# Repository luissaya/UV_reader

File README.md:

# UV reader

Read UV-A and UV-B radiation each minute and save the values with timestamp on an micro SD card.

## Pins

| Pin # | Name      | Pin name | Description                   |
| ----- | --------- | -------- | ----------------------------- |
| 1     | RST       | -        | Reset the chip                |
| 2     | ADC       | A0       | Read the UV sensor            |
| 3     | RESET     | -        | Enable, must be HIGH          |
| 4     | Deepsleep | 16       | Deepsleep, connect to RST pin |
| 5     | CSK       | 14       | SPI pin                       |
| 6     | MISO      | 12       | SPI pin                       |
| 7     | MOSI      | 13       | SPI pin                       |
| 16    | CS        | 15       | SPI pin                       |
| 17    | LED       | 2        | LED, turn on in LOW           |
| 18    | BOOT      | 0        | To flash the firmware         |
| 19    | SDA       | 4        | I2C pin                       |
| 20    | SCL       | 5        | I2C pin                       |
| 21    | RX        | -        | UART pin                      |
| 22    | TX        | -        | UART pin                      |
  
| Label | GPIO   | Input         | Output                | Notes                                                           |
| ----- | ------ | ------------- | --------------------- | --------------------------------------------------------------- |
| D0    | GPIO16 | no interrupt  | no PWM or I2C support | HIGH at boot used to wake up from deep sleep                    |
| D1    | GPIO5  | OK            | OK                    | often used as SCL (I2C)                                         |
| D2    | GPIO4  | OK            | OK                    | often used as SDA (I2C)                                         |
| D3    | GPIO0  | pulled up     | OK                    | connected to FLASH button, boot fails if pulled LOW             |
| D4    | GPIO2  | pulled up     | OK                    | HIGH at bootconnected to on-board LED, boot fails if pulled LOW |
| D5    | GPIO14 | OK            | OK                    | SPI (SCLK)                                                      |
| D6    | GPIO12 | OK            | OK                    | SPI (MISO)                                                      |
| D7    | GPIO13 | OK            | OK                    | SPI (MOSI)                                                      |
| D8    | GPIO15 | pulled to GND | OK                    | SPI (CS), Boot fails if pulled HIGH                             |
| RX    | GPIO3  | OK            | RX pin                | HIGH at boot                                                    |
| TX    | GPIO1  | TX pin        | OK                    | HIGH at boot, debug output at boot, boot fails if pulled LOW    |
| A0    | ADC0   | Analog        | Input                 | X                                                               |

## Calibration

Calculus to obtain the reference voltaje for genering UV intensity:

- `Vref` is the reference value to obtain:
- `Vout`: is read with multimeter.
- `Nread`: is read with ADC.

```bash
Vref = Vout x 1023 / Nread
Vref = 3.684
```

In the main code, put the next expression:  

```bash
Vout = Vref x Nread / 1023
Vout = 3.684 x Nread / 1023
```

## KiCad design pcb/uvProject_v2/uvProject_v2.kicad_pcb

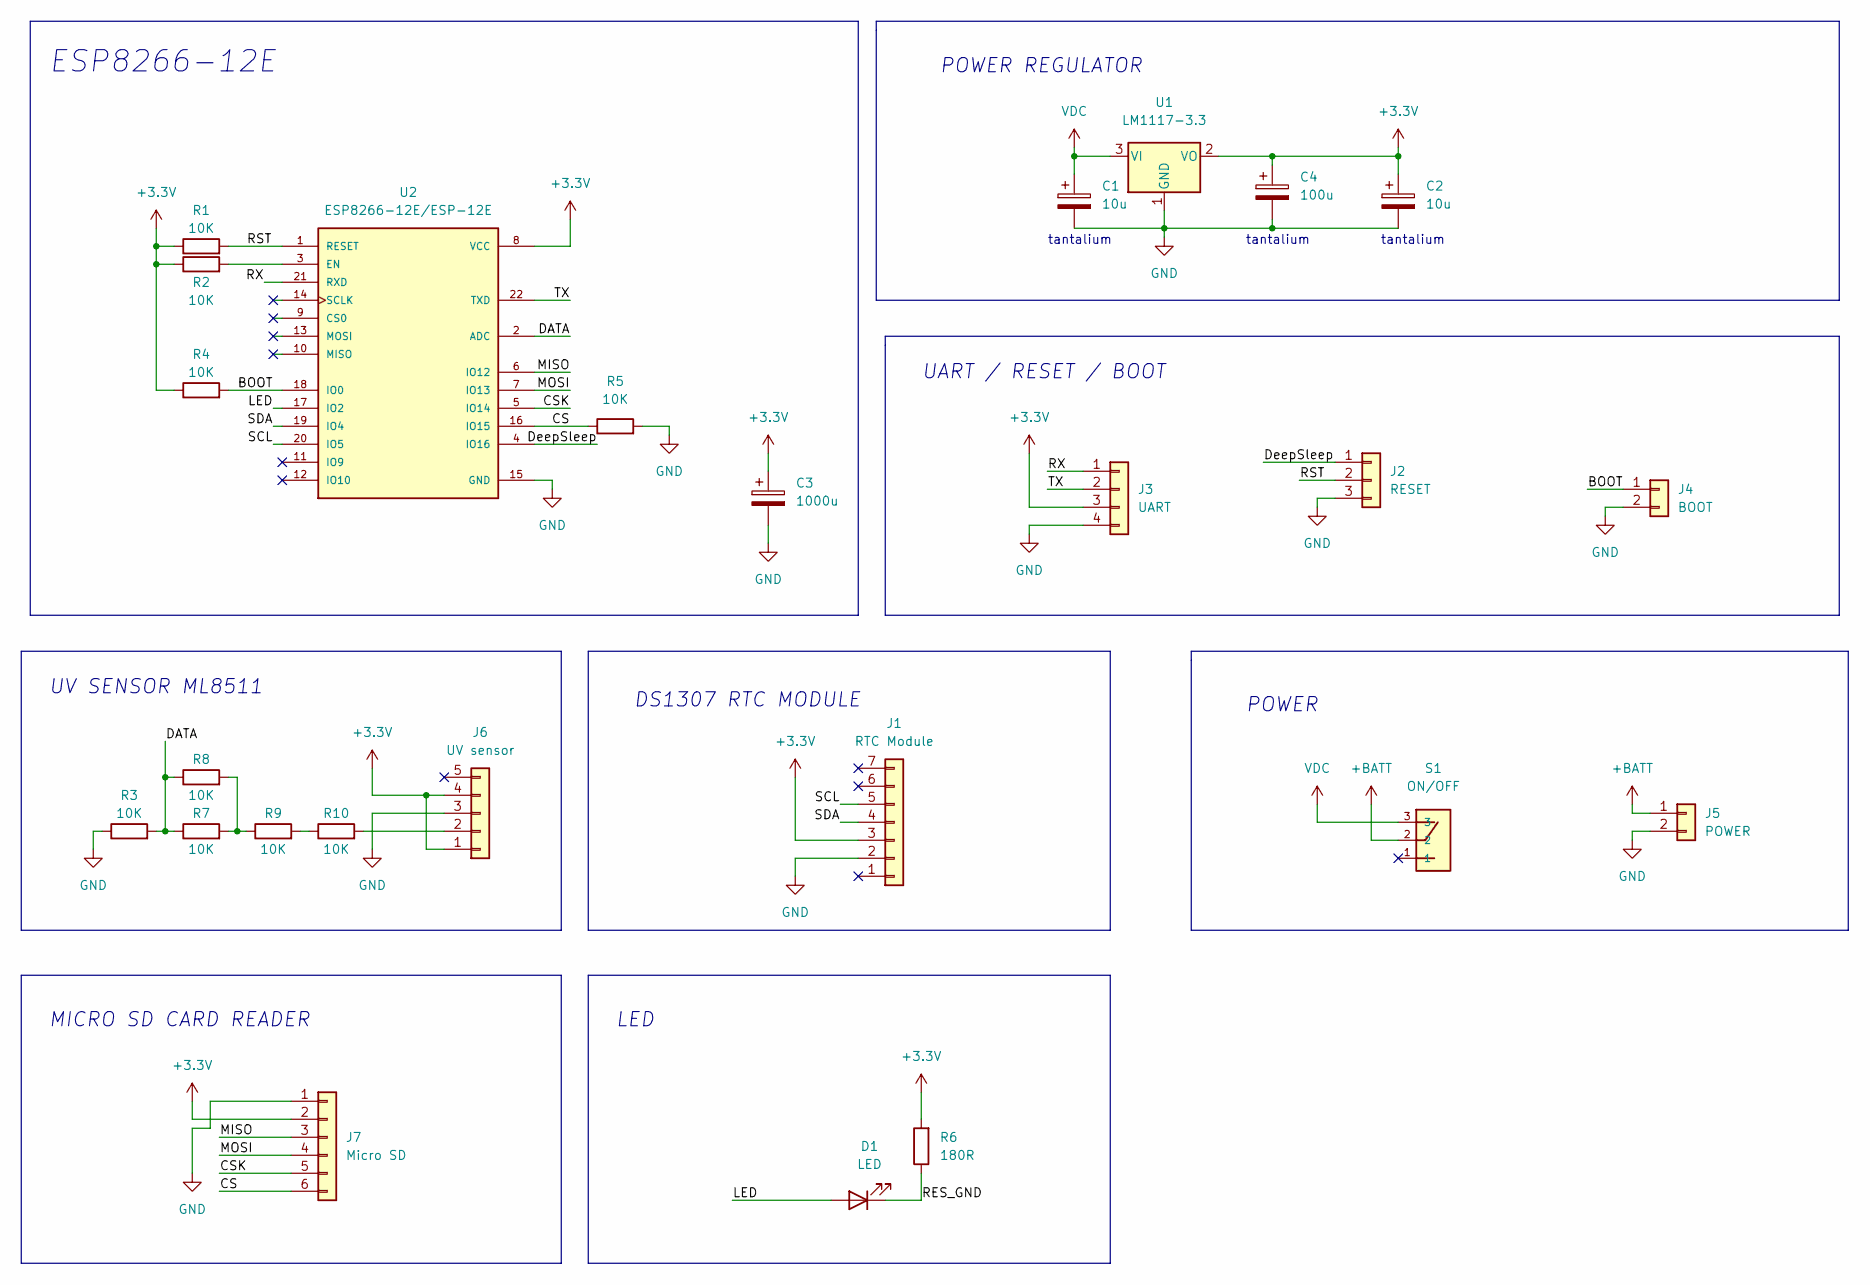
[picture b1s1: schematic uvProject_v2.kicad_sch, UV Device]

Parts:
C1, C2: 10u; C_0603_1608Metric_Pad1.08x0.95mm_HandSolder
C3: 1000u; CP_Radial_D8.0mm_P3.50mm
C4: 100u; C_0805_2012Metric_Pad1.18x1.45mm_HandSolder
D1: LED; LED_D3.0mm
J1: RTC Module; PinHeader_1x07_P2.54mm_Vertical
J2: RESET; PinHeader_1x03_P2.54mm_Vertical
J3: UART; PinSocket_1x04_P2.54mm_Vertical
J4: BOOT; PinHeader_1x02_P2.54mm_Vertical
J5: POWER; PinHeader_1x02_P2.54mm_Vertical
J6: UV sensor; PinSocket_1x05_P2.54mm_Vertical
J7: Micro SD; PinHeader_1x06_P2.54mm_Vertical
R1, R2, R3, R4, R5, R7, R8, R9, R10: 10K; R_1206_3216Metric_Pad1.30x1.75mm_HandSolder
R6: 180R; R_1206_3216Metric_Pad1.30x1.75mm_HandSolder
S1: ON/OFF; SW_OS102011MS2QN1
U1: LM1117-3.3; SOT-223-3_TabPin2
U2: ESP8266-12E/ESP-12E; XCVR_ESP8266-12E_ESP-12E

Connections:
+3.3V: C2.1, C3.1, C4.1, J1.3, J3.3, J6.1, J6.4, J7.2, R1.1, R2.1, R4.1, R6.2, U1.2 (VO), U2.8 (VCC)
+BATT: J5.1, S1.2
/BOOT: J4.1, R4.2, U2.18 (IO0)
/CS: J7.6, R5.1, U2.16 (IO15)
/CSK: J7.5, U2.5 (IO14)
/DATA: R3.2, R7.1, R8.1, U2.2 (ADC)
/DeepSleep: J2.1, U2.4 (IO16)
/LED: D1.2 (A), U2.17 (IO2)
/MISO: J7.3, U2.6 (IO12)
/MOSI: J7.4, U2.7 (IO13)
/RES_GND: D1.1 (K), R6.1
/RST: J2.2, R1.2, U2.1 (RESET)
/RX: J3.1, U2.21 (RXD)
/SCL: J1.5, U2.20 (IO5)
/SDA: J1.4, U2.19 (IO4)
/TX: J3.2, U2.22 (TXD)
GND: C1.2, C2.2, C3.2, C4.2, J1.2, J2.3, J3.4, J4.2, J5.2, J6.3, J7.1, R3.1, R5.2, U1.1 (GND), U2.15 (GND)
unnamed: J6.2, R10.2
unnamed: R7.2, R8.2, R9.1
unnamed: R9.2, R10.1
unnamed: R2.2, U2.3 (EN)
VDC: C1.1, S1.3, U1.3 (VI)

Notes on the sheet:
tantalium
UV SENSOR ML8511
ESP8266-12E
POWER
MICRO SD CARD READER
DS1307 RTC MODULE
LED
UART / RESET / BOOT
POWER REGULATOR

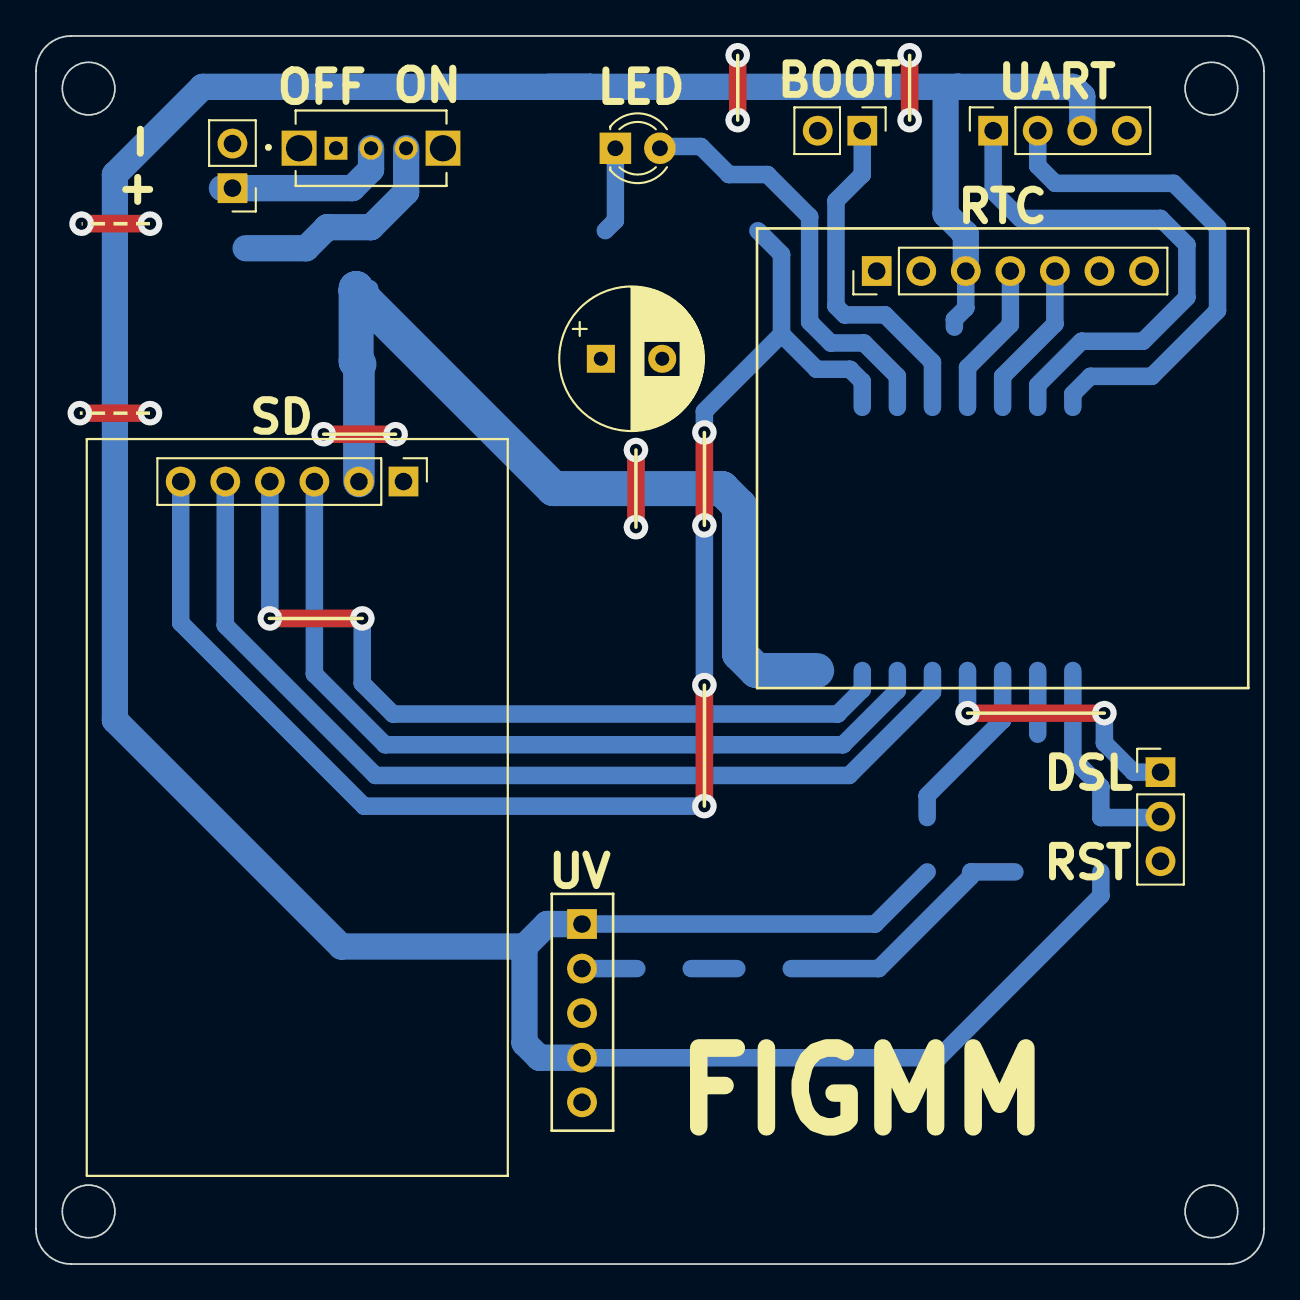
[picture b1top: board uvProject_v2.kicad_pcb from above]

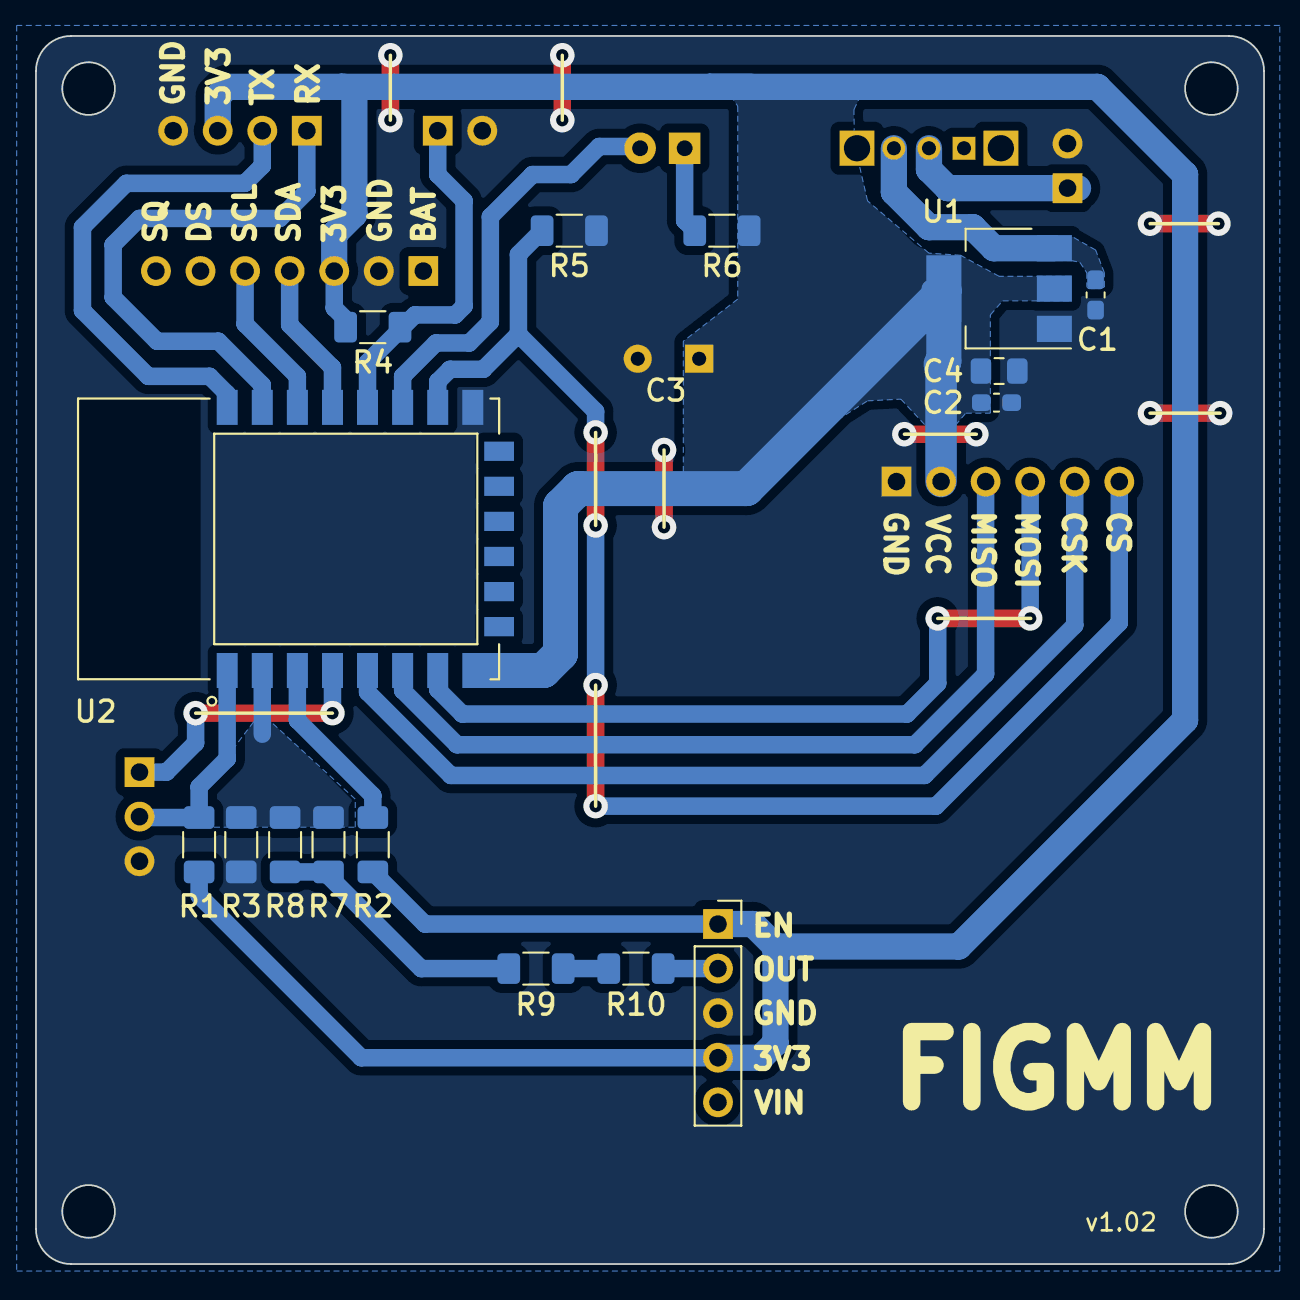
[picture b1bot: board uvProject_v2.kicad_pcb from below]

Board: 2 copper layers, 70.0 x 70.0 mm, 25 parts (16 on the bottom side), 22 nets.

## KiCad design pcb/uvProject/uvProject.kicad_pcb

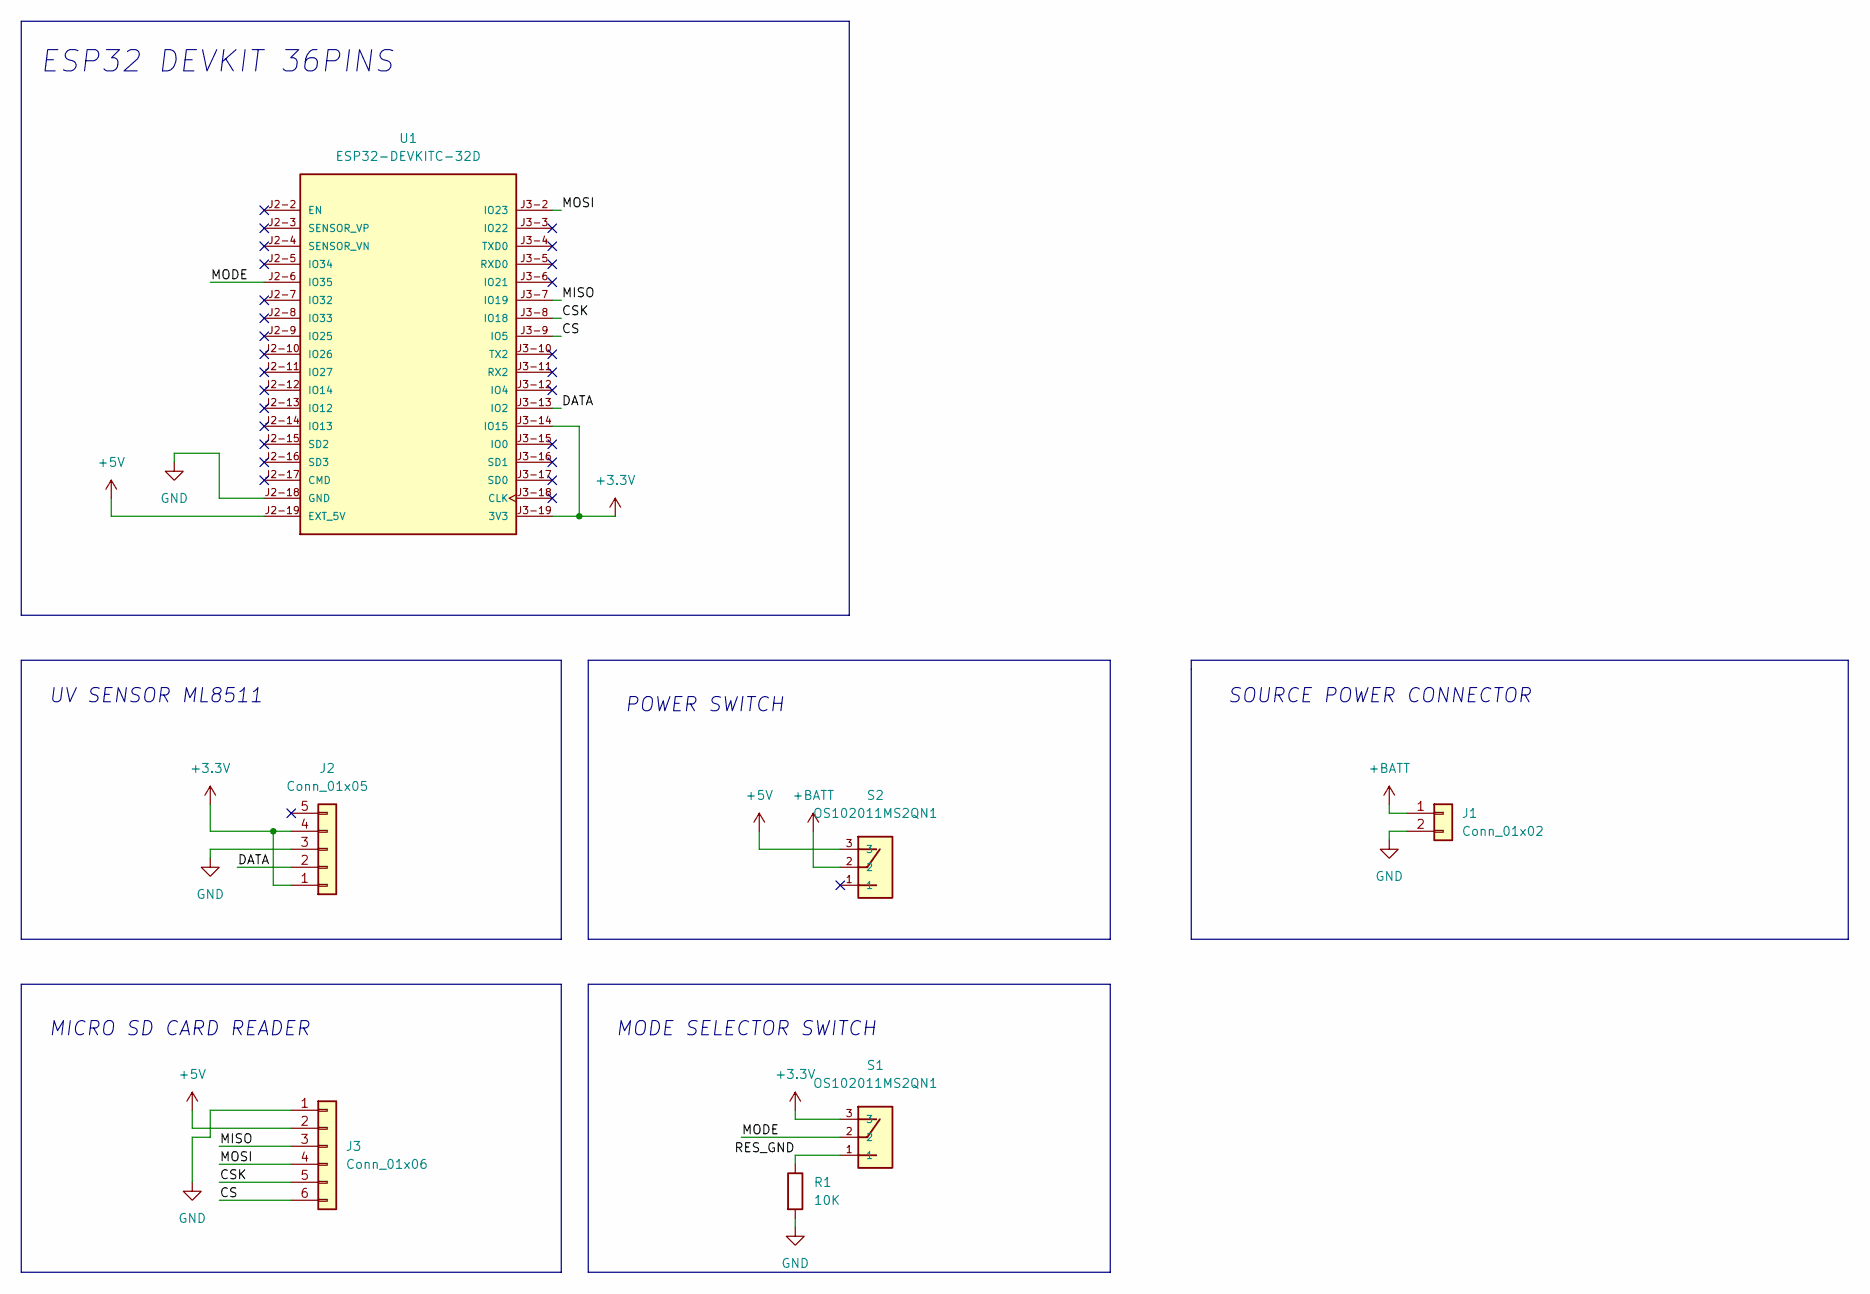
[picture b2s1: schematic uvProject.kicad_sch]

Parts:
J1: Conn_01x02; PinHeader_1x02_P2.54mm_Vertical
J2: Conn_01x05; PinSocket_1x05_P2.54mm_Vertical
J3: Conn_01x06; PinSocket_1x06_P2.54mm_Vertical
R1: 10K; R_Axial_DIN0204_L3.6mm_D1.6mm_P7.62mm_Horizontal
S1, S2: OS102011MS2QN1; SW_OS102011MS2QN1
U1: ESP32-DEVKITC-32D; MODULE_ESP32-DEVKITC-32D; PARTREV V4

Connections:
+3.3V: J2.1, J2.4, S1.3, U1.J3-14 (IO15), U1.J3-19 (3V3)
+5V: J3.2, S2.3, U1.J2-19 (EXT_5V)
+BATT: J1.1, S2.2
/CS: J3.6, U1.J3-9 (IO5)
/CSK: J3.5, U1.J3-8 (IO18)
/DATA: J2.2, U1.J3-13 (IO2)
/MISO: J3.3, U1.J3-7 (IO19)
/MODE: S1.2, U1.J2-6 (IO35)
/MOSI: J3.4, U1.J3-2 (IO23)
/RES_GND: R1.1, S1.1
GND: J1.2, J2.3, J3.1, R1.2, U1.J2-18 (GND)

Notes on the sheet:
ESP32 DEVKIT 36PINS
MODE SELECTOR SWITCH
POWER SWITCH
SOURCE POWER CONNECTOR
UV SENSOR ML8511
MICRO SD CARD READER

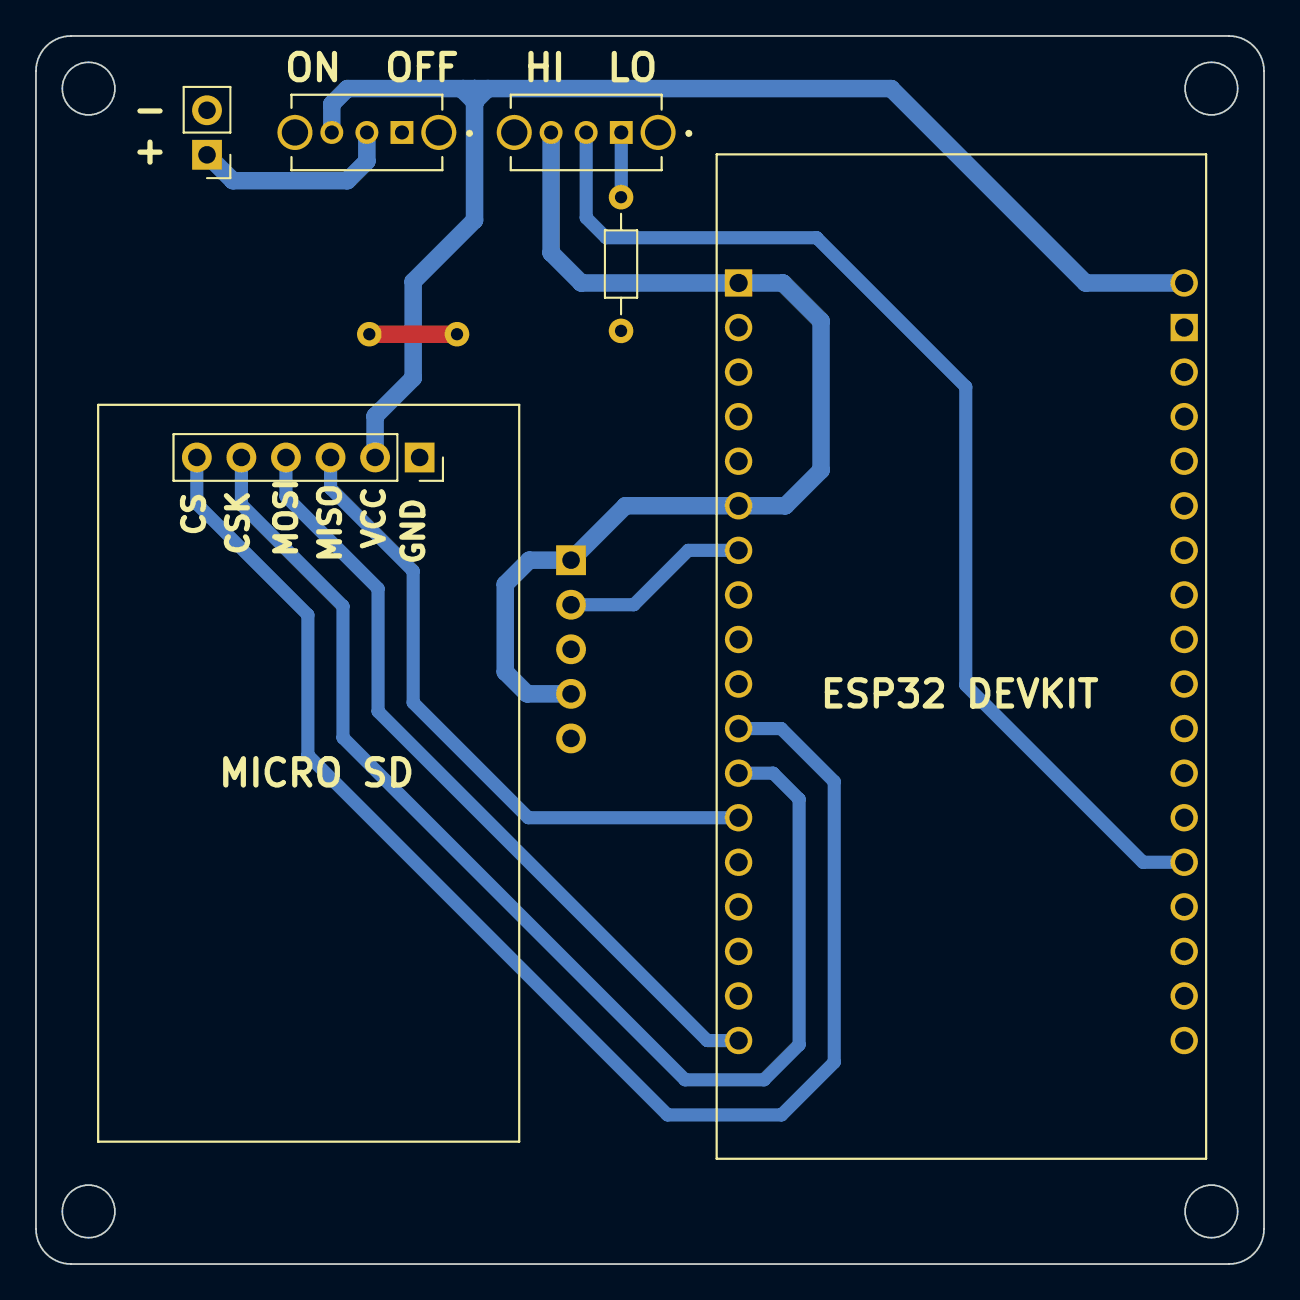
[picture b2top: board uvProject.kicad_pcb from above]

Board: 2 copper layers, 70.0 x 70.0 mm, 7 parts (1 on the bottom side), 11 nets.

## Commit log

2023-10-04 init: initial state
2023-10-09 update:pcb
2023-10-17 fix:firmware
2023-10-20 update: firmware
2023-10-23 chore:readme
2023-11-13 chore: main firmware
2023-11-13 chore: README
2023-11-16 chore: calibration and firmware
